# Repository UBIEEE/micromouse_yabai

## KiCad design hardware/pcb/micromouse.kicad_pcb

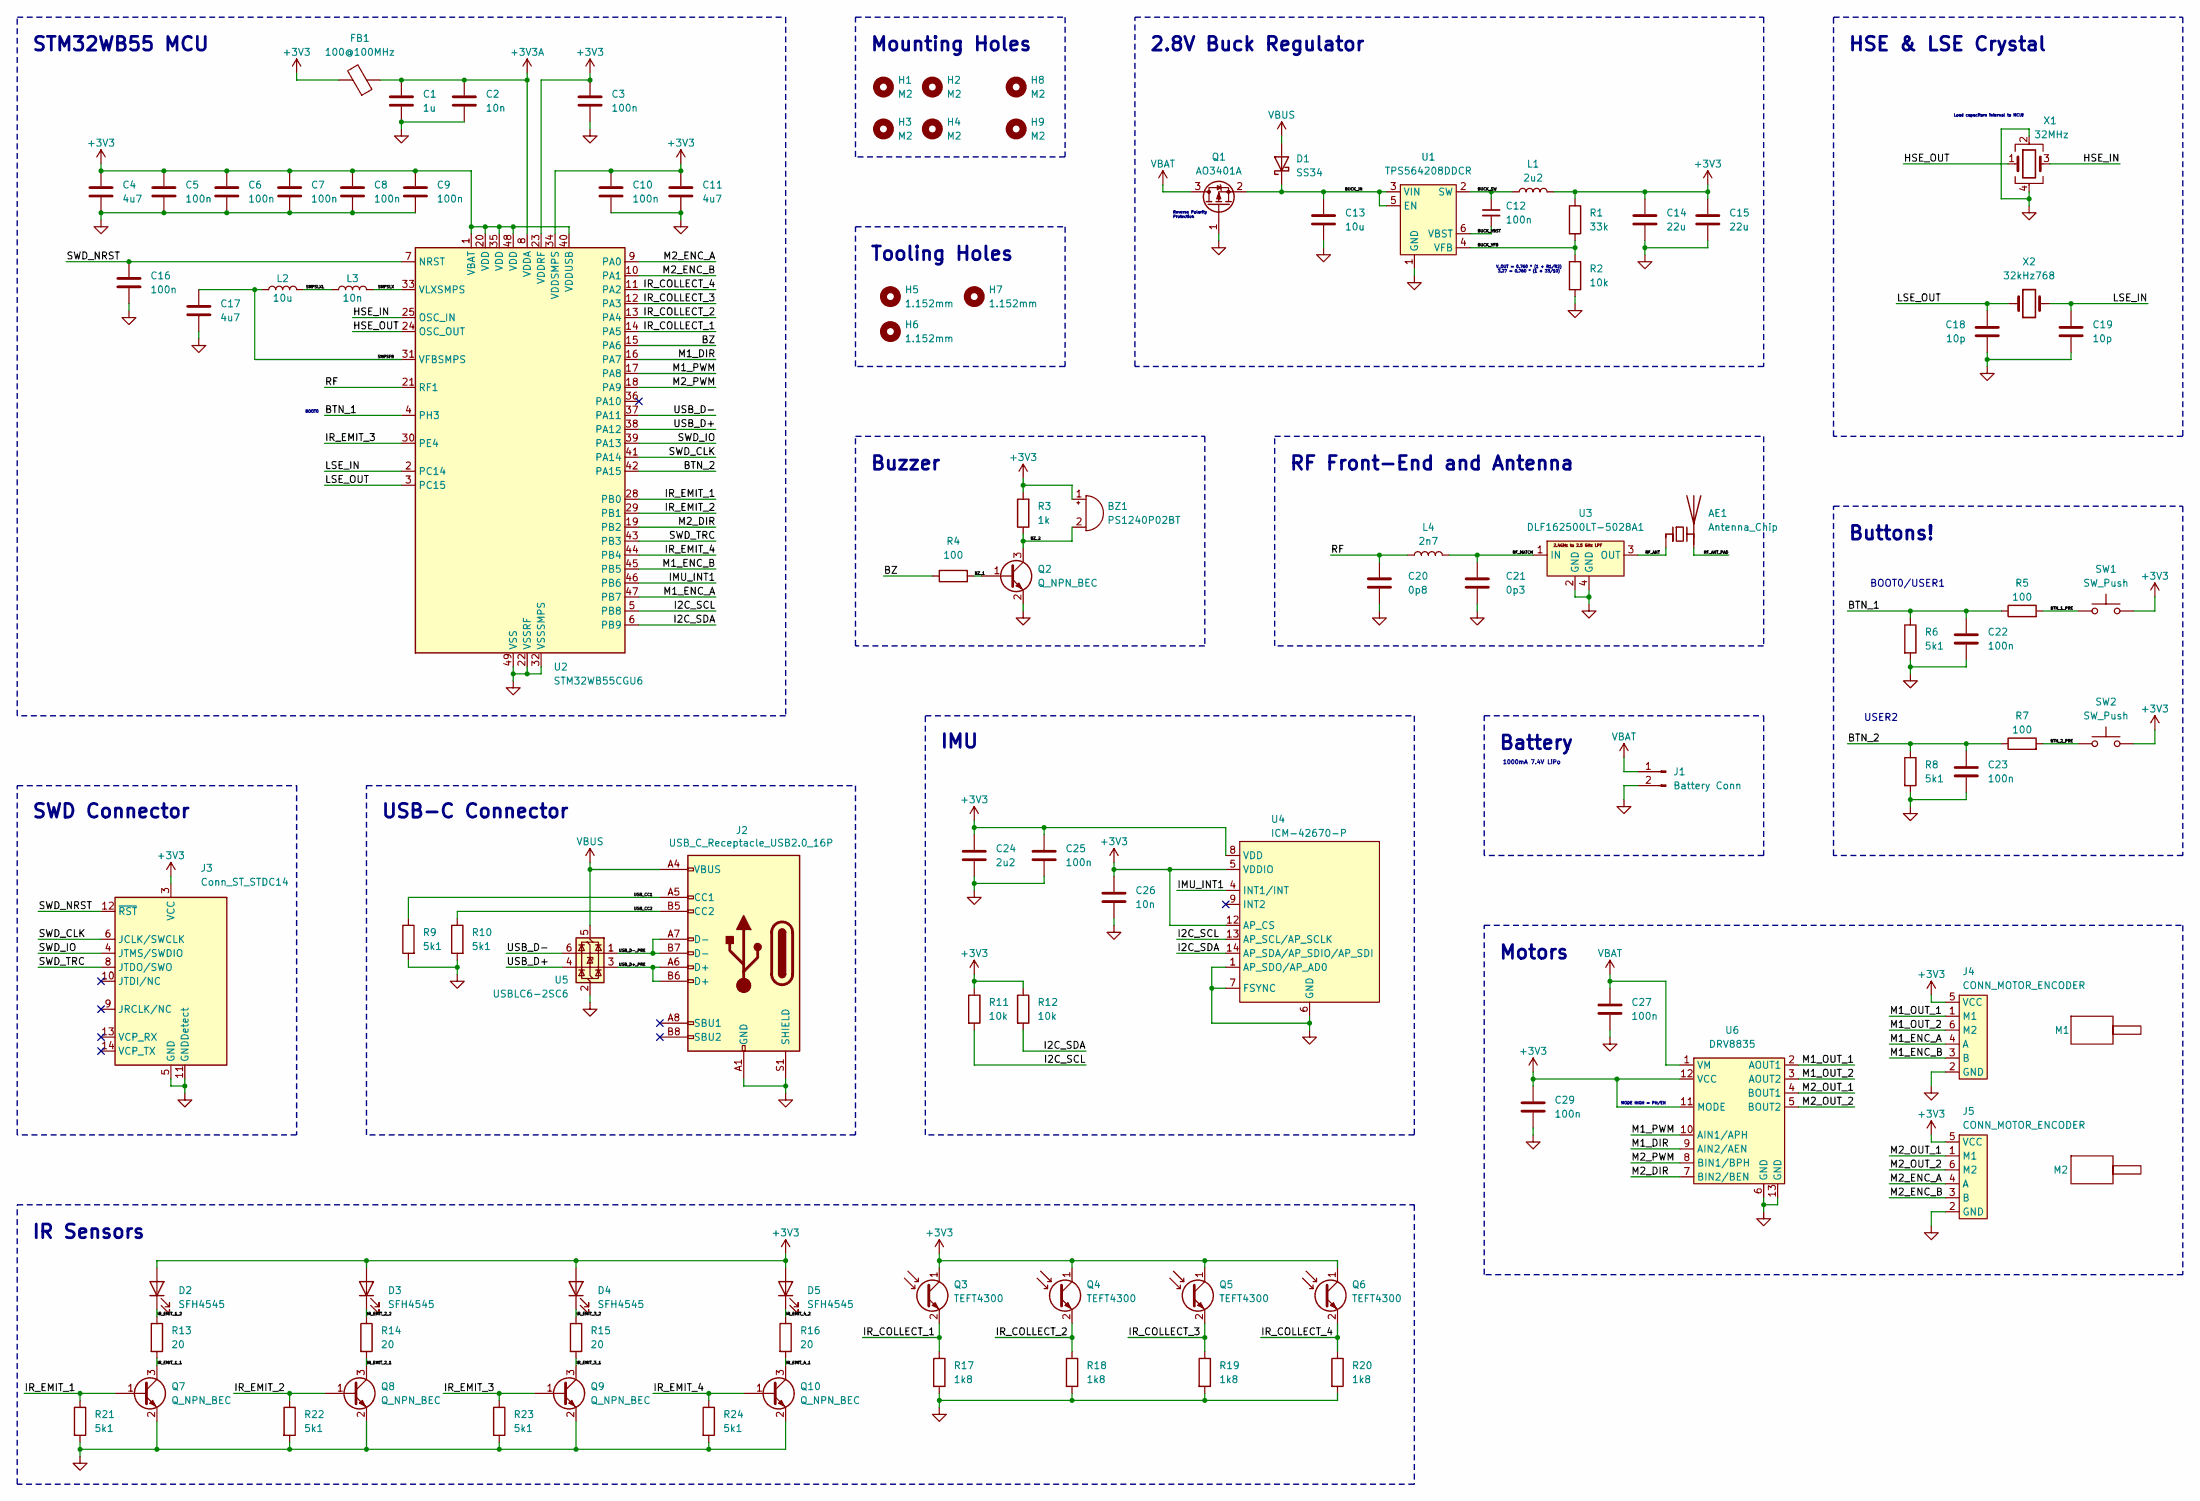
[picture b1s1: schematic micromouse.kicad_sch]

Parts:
AE1: Antenna_Chip; ANT_2450AT42A100E
BZ1: PS1240P02BT
C1: 1u; C_0603_1608Metric; LCSC Part C15849
C2, C26: 10n; C_0402_1005Metric; LCSC Part C15195
C3, C5, C6, C7, C8, C9, C10, C12, C16, C22, C23, C25, C27, C29: 100n; C_0402_1005Metric; LCSC Part C307331
C4, C11, C17: 4u7; C_0603_1608Metric; LCSC Part C19666
C13: 10u; C_1206_3216Metric; LCSC Part C13585
C14, C15: 22u; C_0805_2012Metric; LCSC Part C45783
C18, C19: 10p; C_0402_1005Metric; LCSC Part C32949
C20: 0p8; C_0402_1005Metric_Pad0.74x0.62mm_HandSolder
C21: 0p3; C_0402_1005Metric_Pad0.74x0.62mm_HandSolder
C24: 2u2; C_0603_1608Metric; LCSC Part C23630
D1: SS34; D_SMA; LCSC Part C8678
D2, D4: SFH4545; SFH4545_FLIPPED
D3, D5: SFH4545
FB1: 100@100MHz; D_0805_2012Metric; LCSC Part C1015
H1, H2, H3, H4, H8, H9: M2; MountingHole_2.2mm_M2
H5, H6, H7: 1.152mm; JLC_TOOLING_HOLE
J1: Battery Conn; CONN_BATTERY
J2: USB_C_Receptacle_USB2.0_16P; USB_C_16P_QTGM027; LCSC Part C2681552
J3: Conn_ST_STDC14; SAMTEC_FTSH-107-01-L-DV-K-A
J4, J5: CONN_MOTOR_ENCODER; CONN_BM06B-SRSS-TB_JST
L1: 2u2; L_0805_2012Metric; LCSC Part C383369
L2: 10u; L_0805_2012Metric; LCSC Part C1046
L3: 10n; L_0402_1005Metric; LCSC Part C77103
L4: 2n7; L_0402_1005Metric_Pad0.77x0.64mm_HandSolder
M1, M2: MOTOR_N20
Q1: AO3401A; SOT-23; LCSC Part C15127
Q2, Q7, Q8, Q9, Q10: Q_NPN_BEC; SOT-23; LCSC Part C2150
Q3, Q5: TEFT4300
Q4, Q6: TEFT4300; TEFT4300_FLIPPED
R1: 33k; R_0402_1005Metric; LCSC Part C25779
R2, R11, R12: 10k; R_0402_1005Metric; LCSC Part C25744
R3: 1k; R_0402_1005Metric; LCSC Part C11702
R4, R5, R7: 100; R_0402_1005Metric; LCSC Part C25076
R6, R8, R9, R10, R21, R22, R23, R24: 5k1; R_0402_1005Metric; LCSC Part C25905
R13, R14, R15, R16: 20; R_1206_3216Metric; LCSC Part C17955
R17, R18, R19, R20: 1k8; R_0603_1608Metric; LCSC Part C4177
SW1, SW2: SW_Push; SW_PUSH_1P1T_6x3.5mm_H5.0_APEM_MJTP1250
U1: TPS564208DDCR; TSOT-23-6; LCSC Part C486062
U2: STM32WB55CGU6; QFN-48-1EP_7x7mm_P0.5mm_EP5.6x5.6mm; LCSC Part C404023
U3: DLF162500LT-5028A1; LCSC Part C531364
U4: ICM-42670-P; LCSC Part C3288646
U5: USBLC6-2SC6; SOT-23-6; LCSC Part C2687116
U6: DRV8835; DSS0012A; LCSC Part C129328
X1: 32MHz; XL7EL89CKI-111YLC-32M; LCSC Part C2965582
X2: 32kHz768; Crystal_SMD_3215-2Pin_3.2x1.5mm; LCSC Part C32346

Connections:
+3V3: BZ1.1 (+), C3.1, C4.1, C5.1, C6.1, C7.1, C8.1, C9.1, C10.1, C11.1, C14.1, C15.1, C24.1, C25.1, C26.1, C29.1, D2.2 (A), D3.2 (A), D4.2 (A), D5.2 (A), FB1.2, J3.3 (VCC), J4.5 (VCC), J5.5 (VCC), L1.2, Q3.1 (C), Q4.1 (C), Q5.1 (C), Q6.1 (C), R1.1, R3.2, R11.1, R12.1, SW1.2, SW2.2, U2.1 (VBAT), U2.20 (VDD), U2.23 (VDDRF), U2.34 (VDDSMPS), U2.35 (VDD), U2.40 (VDDUSB), U2.48 (VDD), U4.5 (VDDIO), U4.8 (VDD), U4.12 (AP_CS), U6.11 (MODE), U6.12 (VCC)
+3V3A: C1.1, C2.1, FB1.1, U2.8 (VDDA)
/BTN_1: C22.1, R5.1, R6.1, U2.4 (PH3)
/BTN_1_PRE: R5.2, SW1.1
/BTN_2: C23.1, R7.1, R8.1, U2.42 (PA15)
/BTN_2_PRE: R7.2, SW2.1
/BUCK_IN: C13.1, D1.1 (K), Q1.2 (S), U1.3 (VIN), U1.5 (EN)
/BUCK_SW: C12.1, L1.1, U1.2 (SW)
/BUCK_VBST: C12.2, U1.6 (VBST)
/BUCK_VFB: R1.2, R2.1, U1.4 (VFB)
/BZ: R4.1, U2.15 (PA6)
/BZ_1: Q2.1 (B), R4.2
/BZ_2: BZ1.2 (-), Q2.3 (C), R3.1
/HSE_IN: U2.25 (OSC_IN), X1.3
/HSE_OUT: U2.24 (OSC_OUT), X1.1
/I2C_SCL: R11.2, U2.5 (PB8), U4.13 (AP_SCL/AP_SCLK)
/I2C_SDA: R12.2, U2.6 (PB9), U4.14 (AP_SDA/AP_SDIO/AP_SDI)
/IMU_INT1: U2.46 (PB6), U4.4 (INT1/INT)
/IR_COLLECT_1: Q3.2 (E), R17.1, U2.14 (PA5)
/IR_COLLECT_2: Q4.2 (E), R18.1, U2.13 (PA4)
/IR_COLLECT_3: Q5.2 (E), R19.1, U2.12 (PA3)
/IR_COLLECT_4: Q6.2 (E), R20.1, U2.11 (PA2)
/IR_EMIT_1: Q7.1 (B), R21.1, U2.28 (PB0)
/IR_EMIT_1_1: Q7.3 (C), R13.2
/IR_EMIT_1_2: D2.1 (K), R13.1
/IR_EMIT_2: Q8.1 (B), R22.1, U2.29 (PB1)
/IR_EMIT_2_1: Q8.3 (C), R14.2
/IR_EMIT_2_2: D3.1 (K), R14.1
/IR_EMIT_3: Q9.1 (B), R23.1, U2.30 (PE4)
/IR_EMIT_3_1: Q9.3 (C), R15.2
/IR_EMIT_3_2: D4.1 (K), R15.1
/IR_EMIT_4: Q10.1 (B), R24.1, U2.44 (PB4)
/IR_EMIT_4_1: Q10.3 (C), R16.2
/IR_EMIT_4_2: D5.1 (K), R16.1
/LSE_IN: C19.1, U2.2 (PC14), X2.2
/LSE_OUT: C18.1, U2.3 (PC15), X2.1
/M1_DIR: U2.16 (PA7), U6.9 (AIN2/AEN)
/M1_ENC_A: J4.4 (A), U2.47 (PB7)
/M1_ENC_B: J4.3 (B), U2.45 (PB5)
/M1_OUT_1: J4.1 (M1), U6.2 (AOUT1)
/M1_OUT_2: J4.6 (M2), U6.3 (AOUT2)
/M1_PWM: U2.17 (PA8), U6.10 (AIN1/APH)
/M2_DIR: U2.19 (PB2), U6.7 (BIN2/BEN)
/M2_ENC_A: J5.4 (A), U2.9 (PA0)
/M2_ENC_B: J5.3 (B), U2.10 (PA1)
/M2_OUT_1: J5.1 (M1), U6.4 (BOUT1)
/M2_OUT_2: J5.6 (M2), U6.5 (BOUT2)
/M2_PWM: U2.18 (PA9), U6.8 (BIN1/BPH)
/RF: C20.1, L4.2, U2.21 (RF1)
/RF_ANT: AE1.1 (FEED), U3.3 (OUT)
/RF_ANT_PAD: AE1.2 (PCB_Trace)
/RF_MATCH: C21.1, L4.1, U3.1 (IN)
/SMPSFB: C17.1, L2.1, U2.31 (VFBSMPS)
/SMPSLX: L3.2, U2.33 (VLXSMPS)
/SMPSLXL: L2.2, L3.1
/SWD_CLK: J3.6 (JCLK/SWCLK), U2.41 (PA14)
/SWD_IO: J3.4 (JTMS/SWDIO), U2.39 (PA13)
/SWD_NRST: C16.1, J3.12 (~RST), U2.7 (NRST)
/SWD_TRC: J3.8 (JTDO/SWO), U2.43 (PB3)
/USB_CC1: J2.A5 (CC1), R9.1
/USB_CC2: J2.B5 (CC2), R10.1
/USB_D+: U2.38 (PA12), U5.4 (I/O2)
/USB_D+_PRE: J2.A6 (D+), J2.B6 (D+), U5.3 (I/O2)
/USB_D-: U2.37 (PA11), U5.6 (I/O1)
/USB_D-_PRE: J2.A7 (D-), J2.B7 (D-), U5.1 (I/O1)
GND: C1.2, C2.2, C3.2, C4.2, C5.2, C6.2, C7.2, C8.2, C9.2, C10.2, C11.2, C13.2, C14.2, C15.2, C16.2, C17.2, C18.2, C19.2, C20.2, C21.2, C22.2, C23.2, C24.2, C25.2, C26.2, C27.2, C29.2, J1.2, J2.A1 (GND), J2.A12 (GND), J2.B1 (GND), J2.B12 (GND), J2.S1 (SHIELD), J3.5 (GND), J3.7 (GND), J3.11 (GNDDetect), J4.2 (GND), J5.2 (GND), Q1.1 (G), Q2.2 (E), Q7.2 (E), Q8.2 (E), Q9.2 (E), Q10.2 (E), R2.2, R6.2, R8.2, R9.2, R10.2, R17.2, R18.2, R19.2, R20.2, R21.2, R22.2, R23.2, R24.2, U1.1 (GND), U2.22 (VSSRF), U2.32 (VSSSMPS), U2.49 (VSS), U3.2 (GND), U3.4 (GND), U4.1 (AP_SDO/AP_AD0), U4.6 (GND), U4.7 (FSYNC), U5.2 (GND), U6.6 (GND), U6.13 (GND), X1.2, X1.4
VBAT: C27.1, J1.1, Q1.3 (D), U6.1 (VM)
VBUS: D1.2 (A), J2.A4 (VBUS), J2.A9 (VBUS), J2.B4 (VBUS), J2.B9 (VBUS), U5.5 (VBUS)

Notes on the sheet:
Buzzer
SWD Connector
BOOT0/USER1
Tooling Holes
RF Front-End and Antenna
IR Sensors
USB-C Connector
Buttons!
Reverse Polarity Protection
STM32WB55 MCU
V_OUT = 0.760 * (1 + R1/R2) 3.27 = 0.760 * (1 + 33/10)
HSE & LSE Crystal
IMU
2.8V Buck Regulator
MODE HIGH = PH/EN
1000mA 7.4V LiPo
Motors
Mounting Holes
Battery
USER2
BOOT0
Load capacitors internal to MCU!

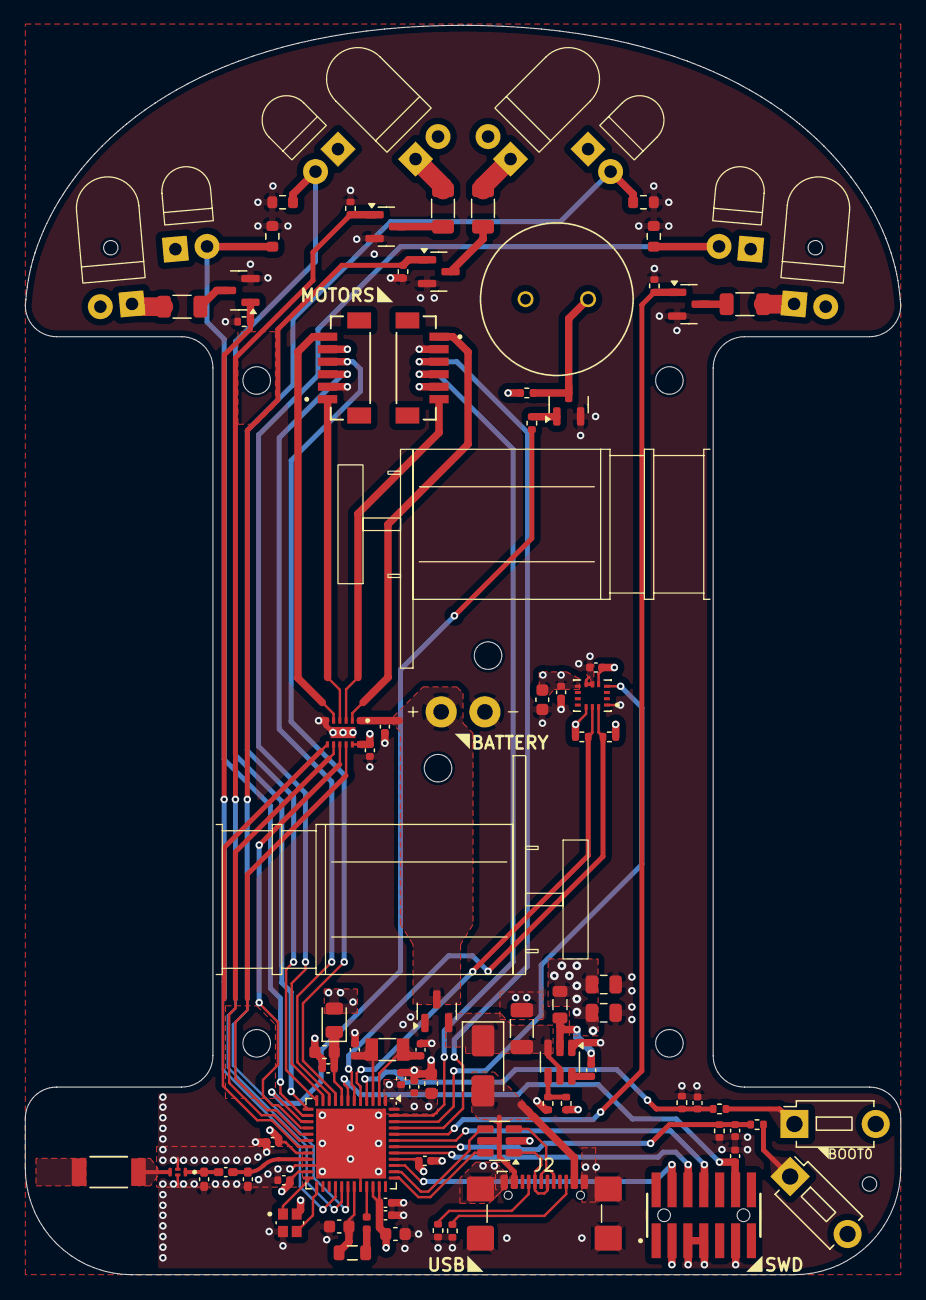
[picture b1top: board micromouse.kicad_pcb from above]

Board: 4 copper layers, 70.0 x 99.9 mm, 100 parts (0 on the bottom side), 67 nets.

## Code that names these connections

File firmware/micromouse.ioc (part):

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Mcu.Name=STM32WB55CGUx
Mcu.Package=UFQFPN48
Mcu.UserName=STM32WB55CGUx
PA0.GPIOParameters=GPIO_Label
PA0.GPIO_Label=ENCODER_RIGHT_A
PA0.Signal=S_TIM2_CH1
PA1.GPIOParameters=GPIO_Label
PA1.GPIO_Label=ENCODER_RIGHT_B
PA1.Signal=S_TIM2_CH2
PA11.Mode=Device
PA11.Signal=USB_DM
PA12.Mode=Device
PA12.Signal=USB_DP
PA13.Mode=Trace_Asynchronous_SW
PA13.Signal=SYS_JTMS-SWDIO
PA14.Mode=Trace_Asynchronous_SW
PA14.Signal=SYS_JTCK-SWCLK
PA15.GPIOParameters=GPIO_Label
PA15.GPIO_Label=BUTTON_2
PA15.Signal=GPXTI15
PA2.GPIOParameters=GPIO_Label
PA2.GPIO_Label=IR_FAR_RIGHT_COLLECT
PA2.Signal=ADCx_IN7
PA3.GPIOParameters=GPIO_Label
PA3.GPIO_Label=IR_MID_RIGHT_COLLECT
PA3.Signal=ADCx_IN8
PA4.GPIOParameters=GPIO_Label
PA4.GPIO_Label=IR_MID_LEFT_COLLECT
PA4.Signal=ADCx_IN9
PA5.GPIOParameters=GPIO_Label
PA5.GPIO_Label=IR_FAR_LEFT_COLLECT
PA5.Signal=ADCx_IN10
PA6.GPIOParameters=GPIO_ModeDefaultPP,GPIO_Speed,GPIO_PuPd,GPIO_Label
PA6.GPIO_Label=BUZZER
PA6.GPIO_ModeDefaultPP=GPIO_MODE_AF_PP
PA6.GPIO_PuPd=GPIO_NOPULL
PA6.GPIO_Speed=GPIO_SPEED_FREQ_LOW
PA6.Signal=S_TIM16_CH1
PA7.GPIOParameters=GPIO_Label
PA7.GPIO_Label=MOTOR_LEFT
PA7.Signal=GPIO_Output
PA8.GPIOParameters=GPIO_Label
PA8.GPIO_Label=MOTOR_LEFT_DIR
PA8.Signal=GPIO_Output
PA9.GPIOParameters=GPIO_Label
PA9.GPIO_Label=MOTOR_RIGHT_DIR
PA9.Signal=GPIO_Output
PB0.GPIOParameters=GPIO_Label
PB0.GPIO_Label=IR_FAR_LEFT_EMIT
PB0.Signal=GPIO_Output
PB1.GPIOParameters=GPIO_Label
PB1.GPIO_Label=IR_MID_LEFT_EMIT
PB1.Signal=GPIO_Output
PB2.GPIOParameters=GPIO_Label
PB2.GPIO_Label=MOTOR_RIGHT
PB2.Signal=GPIO_Output
PB3.Mode=Trace_Asynchronous_SW
PB3.Signal=SYS_JTDO-SWO
PB4.GPIOParameters=GPIO_Label
PB4.GPIO_Label=IR_FAR_RIGHT_EMIT
PB4.Signal=GPIO_Output
PB5.GPIOParameters=GPIO_Label
PB5.GPIO_Label=ENCODER_LEFT_B
PB5.Mode=Encoder_mode_occur1
PB5.Signal=LPTIM1_IN1
PB6.GPIOParameters=GPIO_Label
PB6.GPIO_Label=IMU_INT1
PB6.Signal=GPXTI6
PB7.GPIOParameters=GPIO_Label
PB7.GPIO_Label=ENCODER_LEFT_A
PB7.Mode=Encoder_mode_occur1
PB7.Signal=LPTIM1_IN2
PB8.Mode=I2C
PB8.Signal=I2C1_SCL
PB9.Mode=I2C
PB9.Signal=I2C1_SDA
PC14-OSC32_IN.Mode=LSE-External-Oscillator
PC14-OSC32_IN.Signal=RCC_OSC32_IN
PC15-OSC32_OUT.Mode=LSE-External-Oscillator
PC15-OSC32_OUT.Signal=RCC_OSC32_OUT
PE4.GPIOParameters=GPIO_Label
PE4.GPIO_Label=IR_MID_RIGHT_EMIT
PE4.Signal=GPIO_Output
PH3-BOOT0.GPIOParameters=GPIO_Label
PH3-BOOT0.GPIO_Label=BUTTON_1
PH3-BOOT0.Signal=GPXTI3
RCC.HSE_VALUE=32000000
RCC.SYSCLKFreq_VALUE=64000000
RCC.SYSCLKSource=RCC_SYSCLKSOURCE_PLLCLK
board=custom

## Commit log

2024-04-16 Gitignore
2024-04-16 Added KiCAD Schematic and PCB design
2024-04-17 Created firmware project with STM32CubeMX
2024-04-18 Rearranged MCU pins in schematic and PCB
2024-04-18 Firmware gitignore
2024-04-18 Rearranged MCU pins in STM32CubeMX
2024-04-20 Cleaned up PCB
2024-04-20 Setup visual studio code environment for debugging firmware
2024-04-23 Cleaned up PCB, added tooling holes, etc.
2024-04-23 Rearranged PCB components, added extra mounting holes, removed encoder cutouts, etc.
2024-04-29 Final PCB adjustments
2024-04-30 Added clock model to PCB
2024-04-30 Updated pin assignments in CubeMX
2024-04-30 Firmware: Removed USB stuff for now
2024-04-30 Firmware: Added FreeRTOS
2024-06-05 Finished configuring peripherals in CubeMX
2024-06-13 More configuration in CubeMX
2024-06-13 Registered Robot_Update task with sequencer and set it to execute every 20ms
2024-06-13 Created clang-format
2024-06-13 Added ROBOT_UPDATE_PERIOD_MS constant
2024-06-13 Subsystem class
2024-06-13 Created buzzer class and added startup tone and home depot theme song
2024-06-13 Updated CMakeLists
2024-06-13 Got buttons working with external interrupts
2024-06-13 Created Drive class
2024-06-13 Moved TIM17 callback to drive.cpp
2024-06-13 Created Vision class
2024-06-13 Encoders
2024-06-14 Calculated encoder distance and velocity
2024-06-14 Updated subsystem base class to singleton, cleaned up some comments
2024-06-16 Changed Bluetooth advertising name
2024-06-16 Added Nokia ringtone to buzzer music
2024-06-16 Started dashboard app
2024-06-17 Updated macOS windowing, added Bluetooth disabled view, etc.
2024-06-17 Added not ready view
2024-06-17 Created tabs/sidebar and empty pages, cleaned up some other UI stuff, etc.
2024-06-17 Set up music service and characteristics, fixed some stuff in buzzer class, etc.
2024-06-17 Created music page, read RSSI, and improved Not Ready page
2024-06-17 Added send feedback task to sequencer
2024-06-18 Fixed buzzer quiet function to not crash when called from an interrupt
2024-06-18 Added vision service and notify characteristic
2024-06-18 Added titles to pages
2024-06-18 Created vision page and handled vision service and characteristics
2024-06-19 Added main service and created robot control subsystem, sound on connect/disconnect, send feedback on connect, etc.
2024-06-19 Worked on main page, renamed some files, etc.
2024-06-22 Added drive service
2024-06-22 Worked on drive page, created app icon, etc.
2024-06-25 Changed robot update task to run every 1ms
2024-06-25 Created PID controller class
2024-06-25 Some fixes to encoder counting, started adding pid controllers to drive class, etc.
2024-06-28 Created Error Manager class
2024-06-28 Created standalone singleton class
2024-06-28 Created ICM-42670-P driver class
2024-06-29 Updated IMU driver to use DMA
2024-06-29 Added error code notify characteristic to main service
2024-06-29 Added error codes to error info page
2024-06-29 Cleaned up IMU driver class
2024-06-30 Added characteristics for IMU feedback, send gyro and acceleration data, etc.
2024-06-30 Worked on IMU page
2024-06-30 Cleaned up vision class
2024-06-30 Cleaned up buzzer class
2024-06-30 Added angle data to IMU page
2024-06-30 Differentiated IMU readings to produce angle, sent data over BLE
2024-07-01 Created encoder class and fixed velocity calculation
2024-07-01 Rearranged drive page data
2024-07-02 Changed update period and made encoders simpler
2024-07-07 Worked on adding drive velocity control, fixed encoder things, etc.
2024-07-07 Added test drive task
2024-07-08 Updated main page to add test drive task and stop button
2024-07-08 Updated IMU driver to easier change configuration
2024-07-08 Updated gyro data characteristic size
2024-07-08 Updated gyro data characteristic size, removed angle section from IMU page
2024-07-09 Changed IMU data characteristic, added characteristic for drive PID constants, changed some task stuff, etc.
2024-07-09 Cleaned up several pages, adjusted IMU data characteristic and added page to edit PID constants, etc.
2024-07-12 Created trajectory class
2024-07-12 Cleaned up trajectory class
2024-07-15 Upgrades to C++ 23, because why not?
2024-07-15 Improved drivetrain control modes and PID control method, etc.
2024-07-30 Updated app icons
2024-07-30 Constants
2024-07-30 Created odometry class
2024-07-30 Pose class
2024-07-30 Math functions
2024-07-30 Created timer class
2024-07-30 Made Trajectory class constexpr
2024-07-30 Drive namespace
2024-07-30 Drive Motions
2024-07-30 Drive controllers
2024-07-30 Lots of drive class updates, added odometry to app feedback, etc.
2024-07-30 Added odometry to drive page
2024-07-31 Created navigation library and started maze stuff, added Google tests, etc
2024-07-31 Moved some stuff to navigation library
2024-08-02 Updated BLE characteristics
2024-08-02 Robot control stuff including buttons, reset between tasks, etc.
2024-08-02 Improved IMU standby setting
2024-08-04 Cleaned up maze and cell classes
2024-08-04 Added reset function and maze to solvers
2024-08-04 Small refactor - made subsystems not singletons because it was starting to get confusing, also added some navigation functionality and more!
2024-08-04 More navigation stuff
2024-08-09 Moved more to navigation library, started reworking drive class, added starting position to app, etc.
2024-08-13 Mode navigation work
2024-09-01 Added buzzer songs for search and solve, moved song definitions out of buzzer.cpp
2024-09-01 Added trapezoid profile comments and cleanup
2024-09-01 Created smallest neighbor cell function for Maze
2024-09-01 Added fatal error to error manager for unreachable code
2024-09-02 Task stuff
2024-09-02 Made drive actually stop when stopped
2024-09-02 Drive rotational PID constants
2024-09-02 Repeating songs
2024-09-02 More songs
2024-09-02 Calculated distance to objects with vision sensors
2024-09-02 Added feedback for vision distance calculations
2024-09-02 Implemented the ability to arm tasks and trigger them using vision sensors
2024-09-03 Removed mysterious zero from PID constant
    How did that get there?!?!
2024-09-03 Added back function call to send IMU feedback
2024-09-03 Slowed down IMU sample rate because we don't need it very high
2024-09-05 Updated vision ADC reading to 10-bit
2024-09-05 Renamed RobotDimensions to RobotMeasurements
2024-09-05 Adjusted vision readings based on angle of IR sensors
2024-09-16 added floodfill algorithm, need to check for syntax and correctness
